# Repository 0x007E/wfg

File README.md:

# `WFG` - Waveform Generator (Signalgenerator)

The `WFG` is a board with an [LM324](#additional-information) or any other 4-channel operational amplifier. The board itself is driven with a voltage of `5V`. It generates a triange and a pwm signal. Both signals can be adjustet through the onboard trimmer. When the board is connected to a voltage source the `green` led signals the readiness.

Optional the generated signals can be readin with an external interrupt and a internal running timmer on a microcontroller and status data can be sent to a terminal over UART. A demo how this can be done is attached and can be tested with an [ATmega16A](#additional-information).

> This design is derived form Analog Devices. Details can be found [here](https://www.analog.com/en/resources/design-notes/pulsewidth-modulator-operates-at-various-levels-of-frequency-and-power.html)

| Experience | Level |
|:------------|:-----:|
| Soldering   |  |
| Software    |  |

# Downloads

| Type      | File               | Description              |
|:---------:|:------------------:|:-------------------------|
| Simulation | [asc](https://github.com/0x007E/wfg/raw/refs/heads/main/WFG.asc) | LTSpice Simulation | 
| Lochmaster | [lm4](https://github.com/0x007E/wfg/raw/refs/heads/main/WFG.LM4) | Stripe grid circuit board | 
| Schematic | [pdf](https://github.com/0x007E/wfg/releases/latest/download/schematic.pdf) / [cadlab](https://cadlab.io/project/29870/main/files) | Schematic files |
| Board | [pdf](https://github.com/0x007E/wfg/releases/latest/download/pcb.pdf) / [cadlab](https://cadlab.io/project/29870/main/files) | Board file |
| Drill | [pdf](https://github.com/0x007E/wfg/releases/latest/download/drill.pdf) | Drill file |
| PCB | [zip](https://github.com/0x007E/wfg/releases/latest/download/kicad.zip) / [tar](https://github.com/0x007E/wfg/releases/latest/download/kicad.tar.gz) |  	KiCAD/Gerber/BoM/Drill files |
| Firmware | [zip](https://github.com/0x007E/wfg/releases/latest/download/firmware.zip) / [tar](https://github.com/0x007E/wfg/releases/latest/download/firmware.tar.gz) | Demo Firmware for ATmega16 |

# Hardware

The pcb is created with `KiCAD`. All files are built with `github actions` so that they are ready for a production environment.

## PCB

The circuit board is populated on one side. The best way for soldering the `SMD` components is within a vapor phase soldering system and for the `THT` components with a standard system.

### Top Layer

### Bottom Layer

# Configuration

Within the different trimmers the waveforms can be adjustet in height, frequency and duty cycle.

# Software

The demo firmware (`ATmega16A`) of the `WFG` can be used to measure the frequency and duty cycle of the generated PWM signal and transmit the data over uart to a terminal.

## Dataflow diagram

# Additional Information

| Type       | Link               | Description              |
|:----------:|:------------------:|:-------------------------|
| LM324 | [pdf](https://www.ti.com/lit/ds/symlink/lm324.pdf) | Quad operational amplifier |
| ATmega16A | [pdf](https://ww1.microchip.com/downloads/en/devicedoc/atmel-8154-8-bit-avr-atmega16a_datasheet.pdf) | Microchip ATmega16A Datasheet |

---

R. GAECHTER

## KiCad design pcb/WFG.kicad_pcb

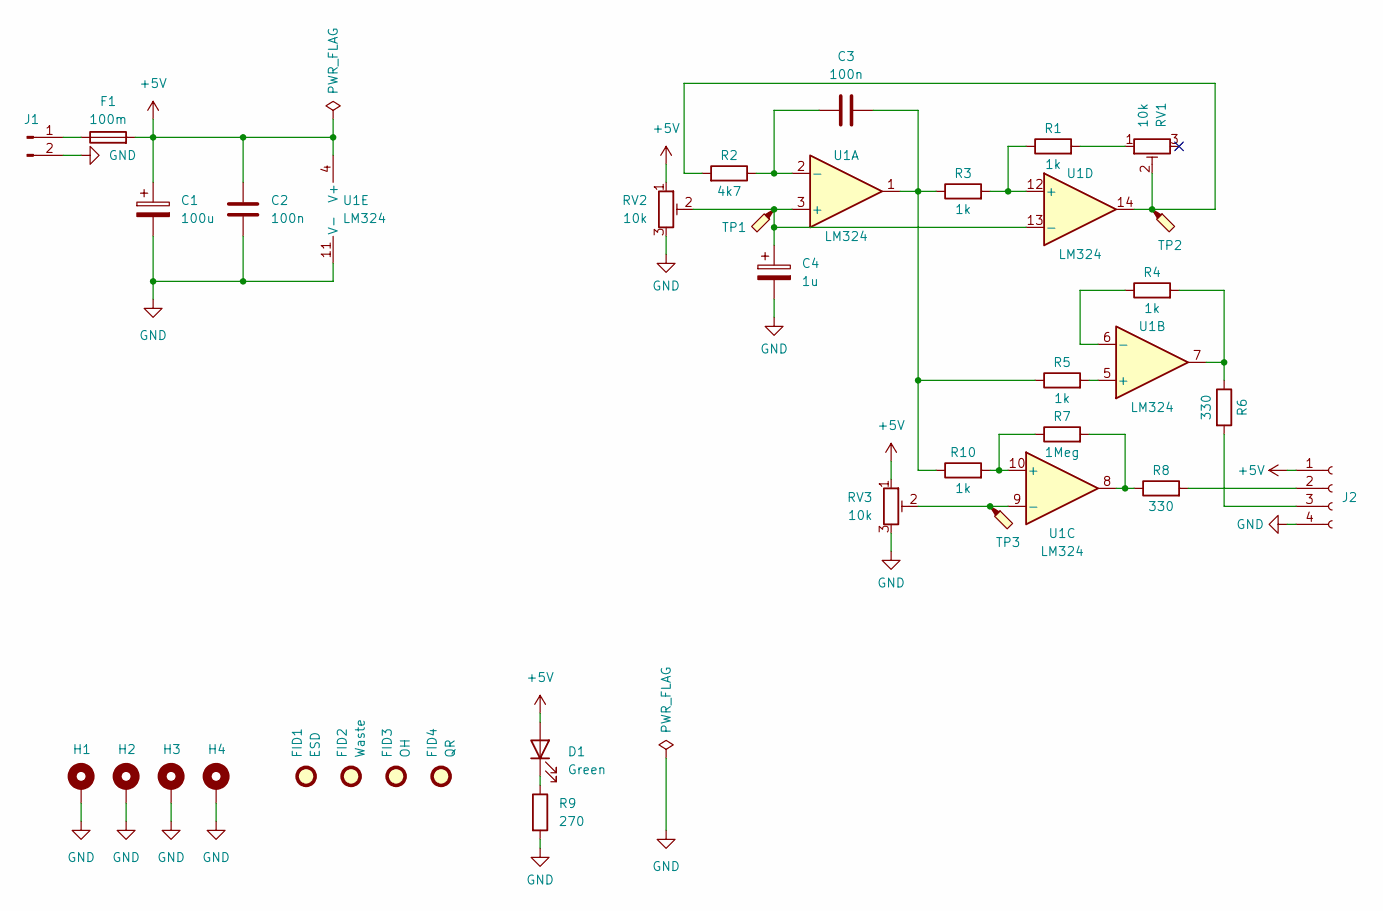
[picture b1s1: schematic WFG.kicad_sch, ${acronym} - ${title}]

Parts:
C1: 100u; CP_Elec_6.3x4.9
C2, C3: 100n; C_1206_3216Metric
C4: 1u; CP_EIA-3528-21_Kemet-B
D1: Green; LED_1206_3216Metric
F1: 100m; Fuse_1206_3216Metric
FID1: ESD; ESD-Logo_6.6x6mm_SilkScreen
FID2: Waste; WEEE-Logo_4.2x6mm_SilkScreen
FID3: OH; OSHW-Logo_5.7x6mm_SilkScreen
FID4: QR; QR_0x007e
H1, H2, H3, H4: MountingHole_Pad; MountingHole_3.2mm_M3_DIN965_Pad
J1: Conn_01x02_Pin; PinHeader_1x02_P2.54mm_Vertical
J2: Conn_01x04_Socket; PinSocket_1x04_P2.54mm_Vertical
R1, R3, R4, R5, R10: 1k; R_1206_3216Metric
R2: 4k7; R_1206_3216Metric
R6, R8: 330; R_1206_3216Metric
R7: 1Meg; R_1206_3216Metric
R9: 270; R_1206_3216Metric
RV1, RV2, RV3: 10k; Potentiometer_Bourns_3296W_Vertical
TP1, TP2, TP3: TestPoint_Probe; TestPoint_Pad_D1.5mm
U1: LM324; SOIC-14_3.9x8.7mm_P1.27mm

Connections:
+5V: C1.1, C2.1, D1.2 (A), F1.2, J2.1, RV2.1, RV3.1, U1.4 (V+)
GND: C1.2, C2.2, C4.2, H1.1, H2.1, H3.1, H4.1, J1.2, J2.4, R9.2, RV2.3, RV3.3, U1.11 (V-)
unnamed: C3.2, R3.1, R5.1, R10.1, U1.1
unnamed: D1.1 (K), R9.1
unnamed: F1.1, J1.1
unnamed: J2.2, R8.2
unnamed: J2.3, R6.2
unnamed: R1.2, RV1.1
unnamed: R2.2, RV1.2, TP2.1, U1.14
unnamed: R4.2, R6.1, U1.7
unnamed: R7.2, R8.1, U1.8
unnamed: C4.1, RV2.2, TP1.1, U1.3 (+), U1.13 (-)
unnamed: C3.1, R2.1, U1.2 (-)
unnamed: R5.2, U1.5 (+)
unnamed: R4.1, U1.6 (-)
unnamed: R7.1, R10.2, U1.10 (+)
unnamed: RV3.2, TP3.1, U1.9 (-)
unnamed: R1.1, R3.2, U1.12 (+)

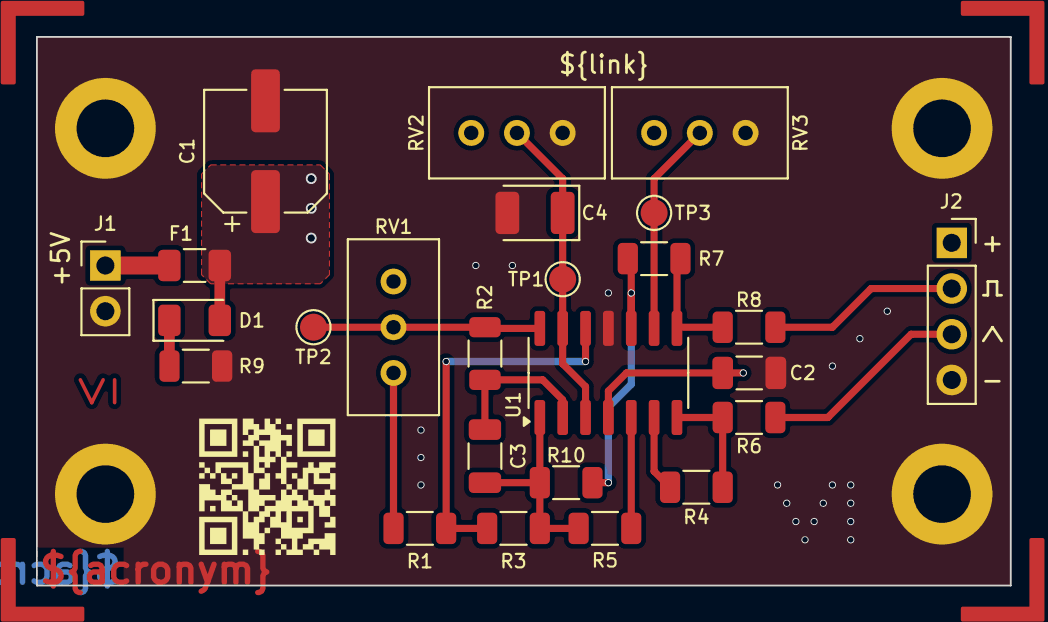
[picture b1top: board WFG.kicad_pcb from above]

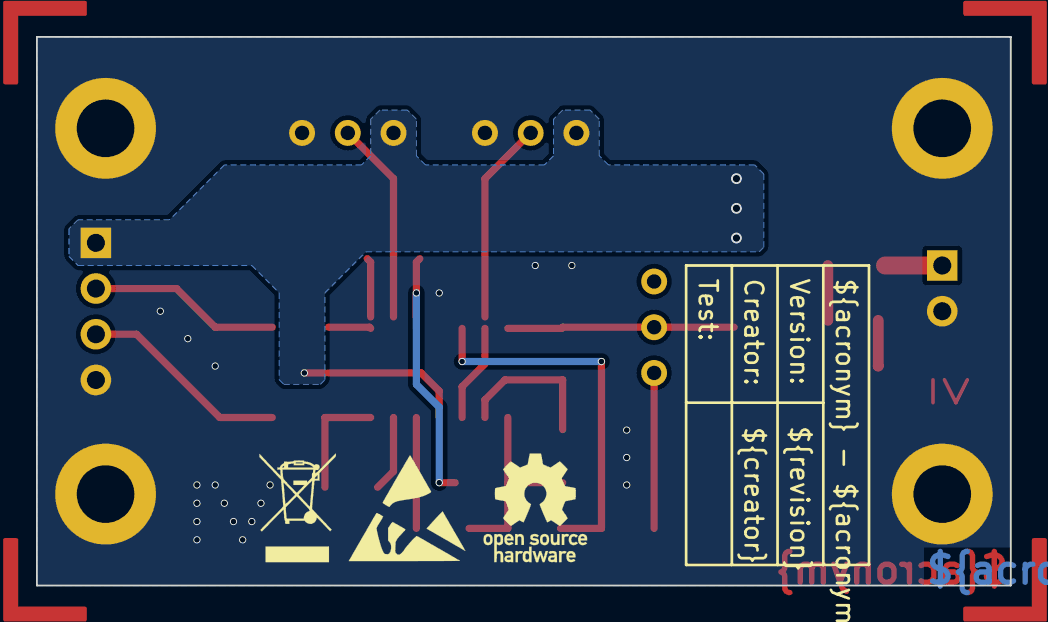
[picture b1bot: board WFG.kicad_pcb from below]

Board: 2 copper layers, 54.1 x 30.5 mm, 33 parts (3 on the bottom side), 18 nets.

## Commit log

2026-01-23 Add spice simulation
2026-01-23 Add lochmaster design
2026-01-23 Add pcb layout
2026-01-23 Add demo firmware
2026-01-23 Add build pipeline
2026-01-23 Add release pipeline
2026-01-23 Add README.md
2026-01-30 Fix LM324 wiring
2026-01-30 Fix wiring fault
2026-02-03 Add images to .gitignore
2026-02-03 Fix naming of part identifiers
2026-02-03 Change gh-actions badge
2026-02-03 Adapt naming of pcb download section
2026-02-03 Add missing vendor
2026-02-03 Add value to build/release pipeline
2026-02-06 Fix typo in LM324 channels
2026-02-06 Fix 0V connection
2026-02-16 Remove unused variables
2026-03-04 Fix fabrication layer layout

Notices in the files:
README.md:
License CC By-NC-SA
parts and their libraries:
license: CC BY-NC-SA 4.0
